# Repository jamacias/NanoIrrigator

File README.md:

# NanoIrrigator
A small Arduino Nano PCB shield for controlling solenoid valves for irrigation systems.

The current design is for a single channel, but may be expanded to more channels if there exists more space.

## Main features
* Single-sided PCB for CNC milling.
* 24VAC solenoid valve control with TRIAC and opto-isolator.
* Snubber circuit.

## Pics

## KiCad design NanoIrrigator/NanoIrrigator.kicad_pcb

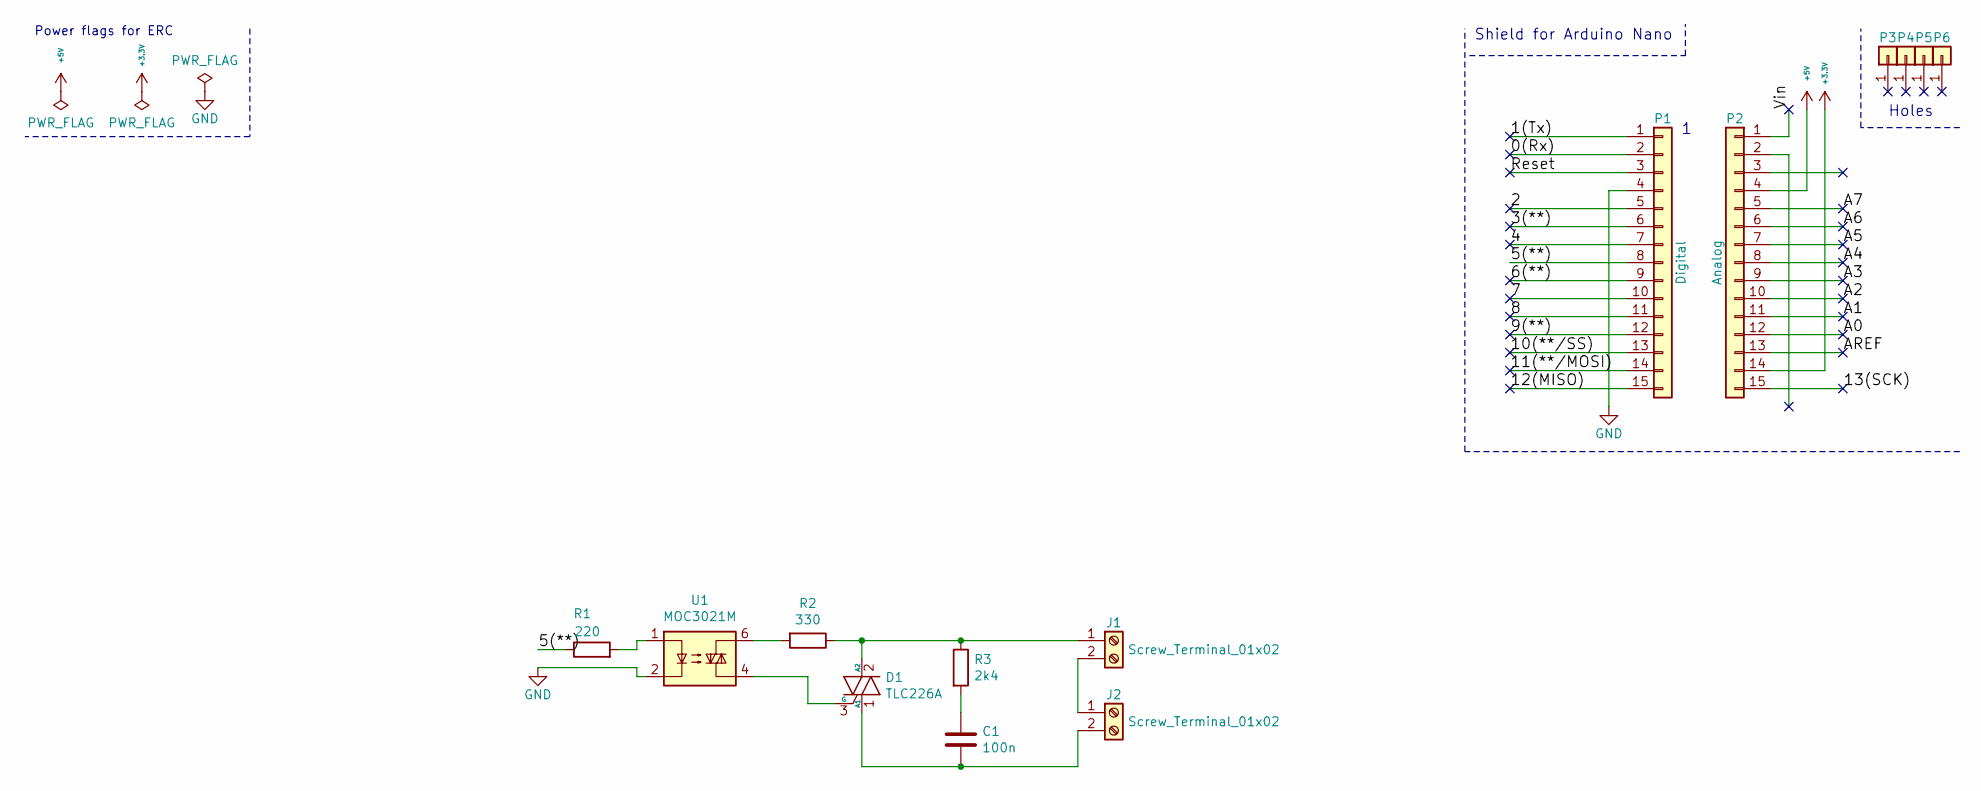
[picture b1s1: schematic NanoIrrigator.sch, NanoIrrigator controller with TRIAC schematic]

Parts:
C1: 100n; C_Disc_D3.0mm_W1.6mm_P2.50mm
D1: TLC226A; TO-220-3_Vertical
J1, J2: Screw_Terminal_01x02; TerminalBlock_bornier-2_P5.08mm
P1: Digital; Socket_Strip_Arduino_1x15
P2: Analog; Socket_Strip_Arduino_1x15
P3, P4, P5, P6: CONN_01X01; 1pin_Nano
R1: 220; R_Axial_DIN0207_L6.3mm_D2.5mm_P2.54mm_Vertical
R2: 330; R_Axial_DIN0207_L6.3mm_D2.5mm_P2.54mm_Vertical
R3: 2k4; R_Axial_DIN0309_L9.0mm_D3.2mm_P2.54mm_Vertical
U1: MOC3021M; DIP-6_W7.62mm_Socket

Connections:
+3V3: P2.14
+5V: P2.4
/0(Rx): P1.2
/1(Tx): P1.1
/2: P1.5
/3(**): P1.6
/4: P1.7
/5(**): P1.8, R1.1
/6(**): P1.9
/7: P1.10
/8: P1.11
/9(**): P1.12
/10(**/SS): P1.13
/11(**/MOSI): P1.14
/12(MISO): P1.15
/13(SCK): P2.15
/A0: P2.12
/A1: P2.11
/A2: P2.10
/A3: P2.9
/A4: P2.8
/A5: P2.7
/A6: P2.6
/A7: P2.5
/AREF: P2.13
/Reset: P1.3
/Vin: P2.1
GND: P1.4, U1.2
unnamed: C1.1, R3.2
unnamed: C1.2, D1.1 (A1), J2.2
unnamed: D1.2 (A2), J1.1, R2.1, R3.1
unnamed: D1.3 (G), U1.4
unnamed: J1.2, J2.1
unnamed: R1.2, U1.1
unnamed: R2.2, U1.6

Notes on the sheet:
Holes
Shield for Arduino Nano
Power flags for ERC

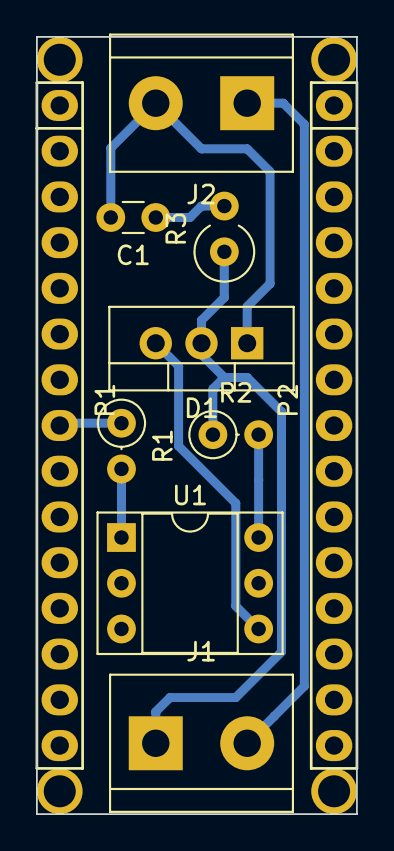
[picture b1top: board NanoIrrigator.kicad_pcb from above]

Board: 2 copper layers, 17.8 x 43.2 mm, 14 parts (0 on the bottom side), 9 nets.

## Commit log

2020-04-12 Added project files and documentation.
2020-04-12 Fixed README.
